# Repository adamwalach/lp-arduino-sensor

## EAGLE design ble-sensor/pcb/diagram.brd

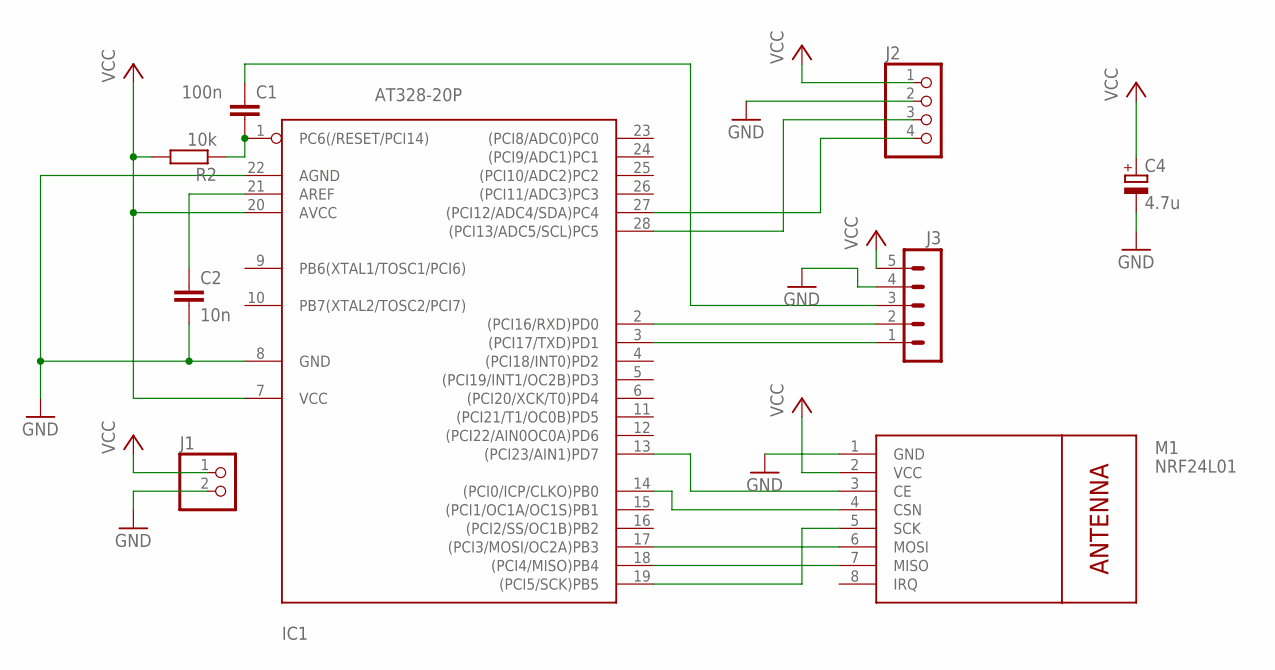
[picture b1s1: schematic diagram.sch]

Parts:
C1: 100n; C050-024X044
C2: 10n; C050-024X044
C4: 4.7u; E1,8-4
IC1: AT328-20P; DIL28-3
J1: PINHD-1X2; 1X02
J2: PINHD-1X4; 1X04
J3: MA05-1
M1: NRF24L01; WIRELESS-NRF24L01
R2: 10k; 0204/7

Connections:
GND: C2.2, C4.-, IC1.8 (GND), IC1.22 (AGND), J1.2, J2.2, J3.4, M1.1 (GND)
unnamed: C1.2, IC1.1 (PC6(/RESET/PCI14)), R2.1
unnamed: IC1.18 ((PCI4/MISO)PB4), M1.7 (MISO)
unnamed: IC1.19 ((PCI5/SCK)PB5), M1.5 (SCK)
unnamed: IC1.17 ((PCI3/MOSI/OC2A)PB3), M1.6 (MOSI)
unnamed: IC1.3 ((PCI17/TXD)PD1), J3.1
unnamed: IC1.2 ((PCI16/RXD)PD0), J3.2
unnamed: IC1.28 ((PCI13/ADC5/SCL)PC5), J2.3
unnamed: C1.1, J3.3
unnamed: IC1.27 ((PCI12/ADC4/SDA)PC4), J2.4
unnamed: IC1.14 ((PCI0/ICP/CLKO)PB0), M1.4 (CSN)
unnamed: IC1.13 ((PCI23/AIN1)PD7), M1.3 (CE)
unnamed: C2.1, IC1.21 (AREF)
VCC: C4.+, IC1.7 (VCC), IC1.20 (AVCC), J1.1, J2.1, J3.5, M1.2 (VCC), R2.2

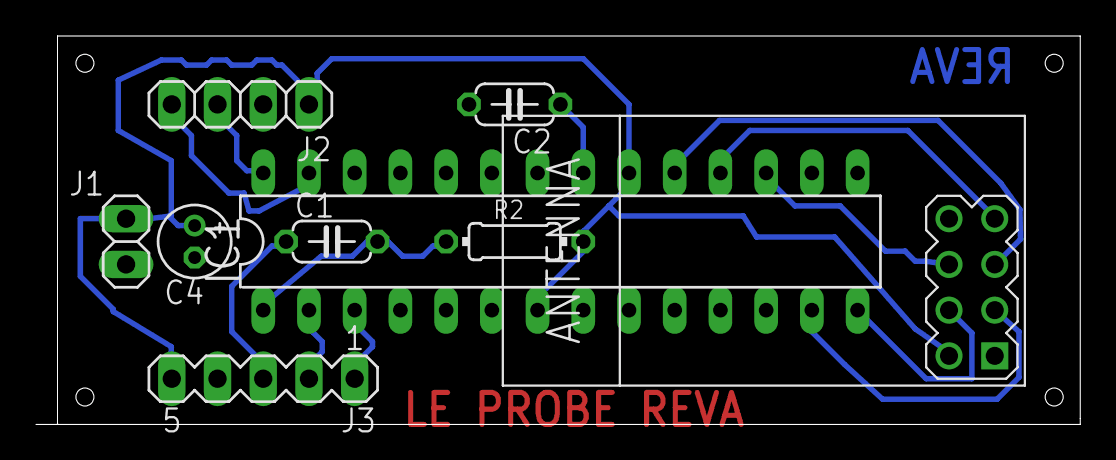
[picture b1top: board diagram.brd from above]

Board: 2 copper layers, 58.0 x 21.6 mm, 9 parts (0 on the bottom side), 14 nets.

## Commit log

2017-08-03 add gateway schematic

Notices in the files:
parts and their libraries:
diy-modules: Released under the Creative Commons Attribution 4.0 International License: http://creativecommons.org/licenses/by/4.0
